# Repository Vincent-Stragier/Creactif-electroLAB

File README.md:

# Créactif(s) && electroLAB

Documents utilisés lors des séances Créactifs! dispensées par l'electroLAB.

Dans ce Git, vous retrouverez nos slides, nos projets et nos codes sources.

Historiquement, nous donnions des séances relatives à la conception d'une matrice de LED et une autre relative à la miniaturisation de vos projets. Depuis la fin de l'année 2022, nous dispensons deux séances relatives à la matrice de LED et deux portant sur l'utilisation des ordinateurs monocartes Raspberry.

## Séances
Dans les deux premières séances ([Matrice de LED](#seance_led)), l'objectif est de comprendre comment le mutiplexage fonctionne et implémenter une sorte de [pilote](https://fr.wikipedia.org/wiki/Pilote_informatique) afin d'afficher des [_pixel arts_](https://fr.wikipedia.org/wiki/Pixel_art) ou des animations en _pixel art_.

Anciennement, une dernière séance ([Miniaturisation avec l'ATtiny](#seance_attiny)), était consacrée à l'utilisation de l'ATtiny 85 afin d'apprendre à miniaturiser les projets à base d'Arduino.

Depuis 2022, nous essayons d'introduire à nouveau les ordinateurs monocartes de Raspberry Pi ([Séances Raspberry Pi](#seance_rpi)). Le contenu est assez réduit à l'heure actuelle (installation du système d'exploitation, prise en main de SSH et de Raspberry Pi OS, interaction avec les broches, etc.).

### Matrice de LED
Deux séances sont données pour l'atelier sur la matrice de LED :
 - [slides de la première partie](/Séances_Matrice_de_LED/Slides/multiplex_part1/slides_1.pdf) ;
 - [slides de la seconde partie](/Séances_Matrice_de_LED/Slides/multiplex_part2/slides_2.pdf).
 
Des [codes exemple](Séances_Matrice_de_LED/Code) sont disponibles (deux projets Arduino et un projet Platformio sont proposés).

### Miniaturisation avec l'ATtiny

La miniaturisation des projets Arduino à l'aide de l'ATtiny 85 présentée en une séance. Les slides sont disponibles [ici](/Séance_ATtiny85/Slides/ATtiny85.pdf).

### Séances Raspberry Pi

Les séances relatives aux ordinateurs monocartes Raspberry Pi portent sur l'installation du système d'exploitation, la connexion en SSH ou via VNC, l'utilisation de différentes commandes dans le terminal (via VNC ou SSH), l'interaction avec les broches (via le système de fichiers, C++ ou Python) et réalisation d'un petit projet d'interface graphique.

Les slides sont disponibles [ici](/Séances_Raspberry_Pi/RPi.pdf).

En outre, par simplicité un guide de démarrage rapide est disponible [ici](/Séances_Raspberry_Pi/quickstart.md).

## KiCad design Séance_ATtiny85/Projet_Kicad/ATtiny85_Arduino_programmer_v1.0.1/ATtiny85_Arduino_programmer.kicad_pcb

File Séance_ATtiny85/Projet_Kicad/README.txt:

ATtiny85_Arduino_programmer

Note de version :

[v1.0.0] 
	- Shield fonctionnel pour programmer l'ATtiny85 avec une carte Arduino Uno
	
[v1.0.1]
	- Changement du silkscreen de l'empreinte du shield (suppression du contour)

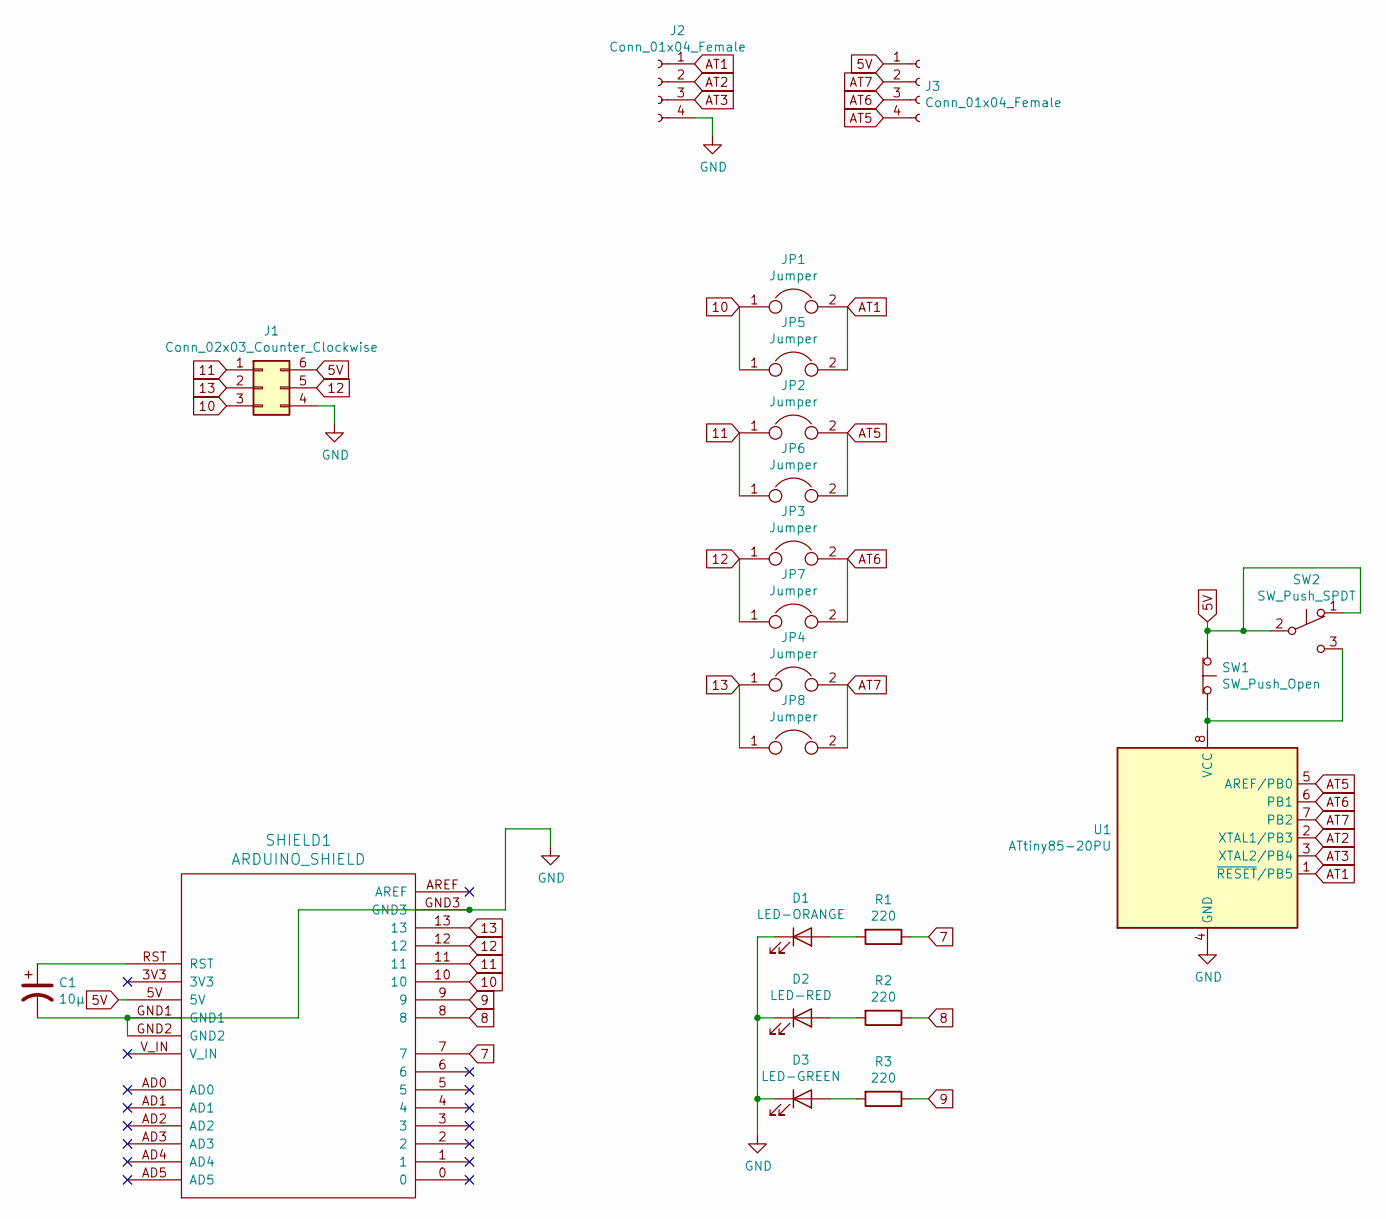
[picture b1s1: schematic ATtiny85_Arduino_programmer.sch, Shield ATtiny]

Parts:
C1: 10µ; CP_Radial_D6.3mm_P2.50mm
D1: LED-ORANGE; LED_1206_HandSoldering
D2: LED-RED; LED_1206_HandSoldering
D3: LED-GREEN; LED_1206_HandSoldering
J1: Conn_02x03_Counter_Clockwise; Pin_Header_Straight_2x03_Pitch2.54mm
J2, J3: Conn_01x04_Female; Pin_Header_Straight_1x04_Pitch2.54mm
JP1, JP2, JP3, JP4: Jumper; Pin_Header_Straight_1x02_Pitch2.54mm
JP5, JP6, JP7, JP8: Jumper; SolderJumper-2_P1.3mm_Open_Pad1.0x1.5mm
R1, R2, R3: 220; R_1210_HandSoldering
SHIELD1: ARDUINO_SHIELD; ARDUINO_SHIELD_040pins
SW1: SW_Push_Open; SW_PUSH_6mm
SW2: SW_Push_SPDT; Pin_Header_Straight_1x03_Pitch2.54mm
U1: ATtiny85-20PU; DIP-8_W7.62mm_LongPads

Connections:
5V: J1.6, J3.1, SHIELD1.5V, SW1.1 (A), SW2.1 (A), SW2.2 (B)
7: R1.1, SHIELD1.7
8: R2.1, SHIELD1.8
9: R3.1, SHIELD1.9
10: J1.3, JP1.1, JP5.1, SHIELD1.10
11: J1.1, JP2.1, JP6.1, SHIELD1.11
12: J1.5, JP3.1, JP7.1, SHIELD1.12
13: J1.2, JP4.1, JP8.1, SHIELD1.13
AT1: J2.1, JP1.2, JP5.2, U1.1 (~RESET~/PB5)
AT2: J2.2, U1.2 (XTAL1/PB3)
AT3: J2.3, U1.3 (XTAL2/PB4)
AT5: J3.4, JP2.2, JP6.2, U1.5 (AREF/PB0)
AT6: J3.3, JP3.2, JP7.2, U1.6 (PB1)
AT7: J3.2, JP4.2, JP8.2, U1.7 (PB2)
GND: C1.2, D1.1 (K), D2.1 (K), D3.1 (K), J1.4, J2.4, SHIELD1.GND1, SHIELD1.GND2, SHIELD1.GND3, U1.4 (GND)
unnamed: C1.1, SHIELD1.RST
unnamed: D1.2 (A), R1.2
unnamed: D2.2 (A), R2.2
unnamed: D3.2 (A), R3.2
unnamed: SW1.2 (B), SW2.3 (C), U1.8 (VCC)

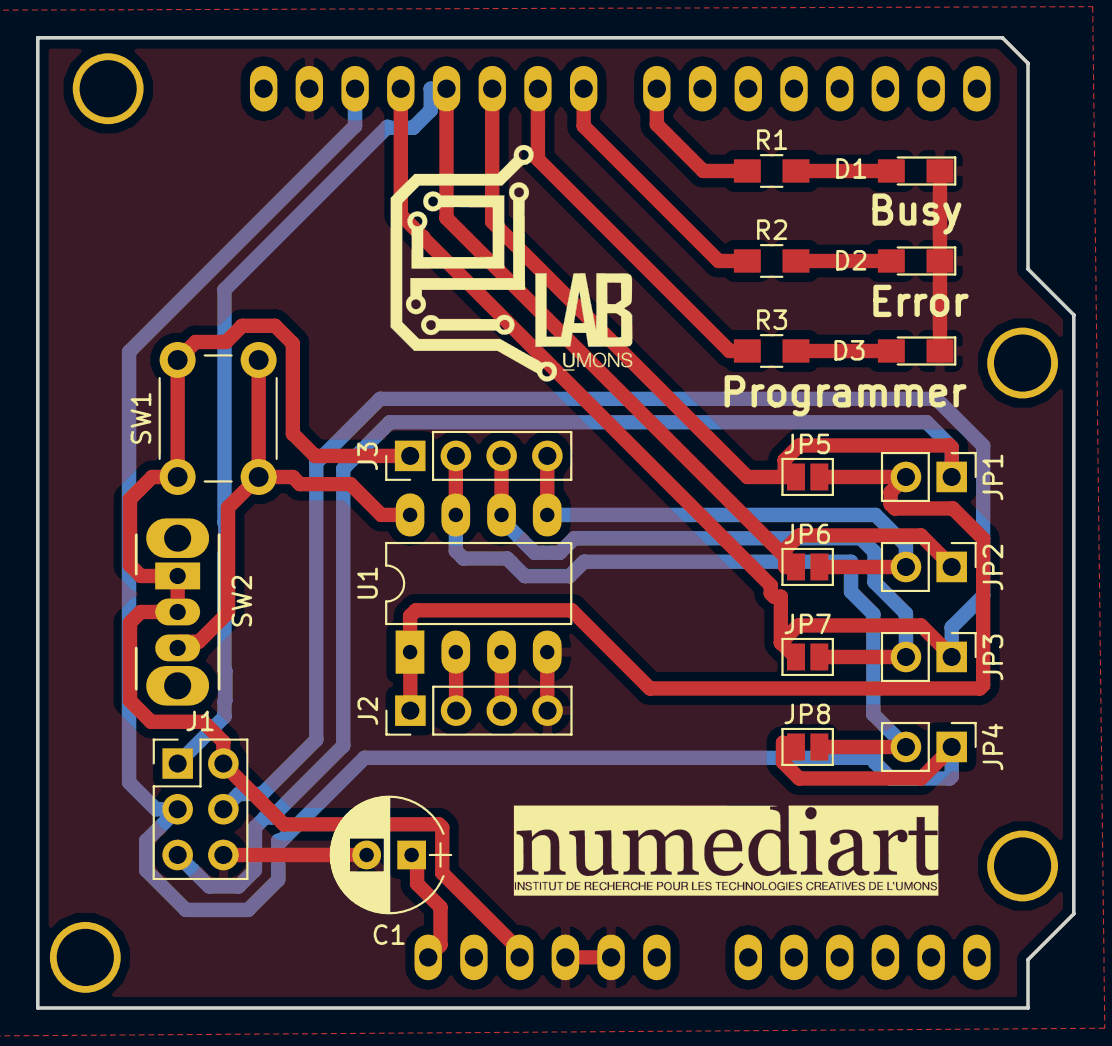
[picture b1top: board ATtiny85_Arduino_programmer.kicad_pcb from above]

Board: 2 copper layers, 57.6 x 53.9 mm, 22 parts (0 on the bottom side), 20 nets.

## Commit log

2019-04-06 Add LED matrix content
2021-12-21 Update slides
2022-12-14 Ajout des slides, changement du nom de dossier, etc.
2022-12-14 Ajout d'information sur la Raspberry Pi.
2022-12-14 Complétion du guide RPi.
2022-12-14 Ajout des étapes d'installation.
2022-12-15 Ajout d'informations relatives à l'installation.
